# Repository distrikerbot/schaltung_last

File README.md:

# schaltung_last
Schaltung_Last_clean:
KiCad Schemantik and Design of the Digital Power Supply

schaltung_last:
Code from CubeIDE

TODO:
rename file names to be clearer

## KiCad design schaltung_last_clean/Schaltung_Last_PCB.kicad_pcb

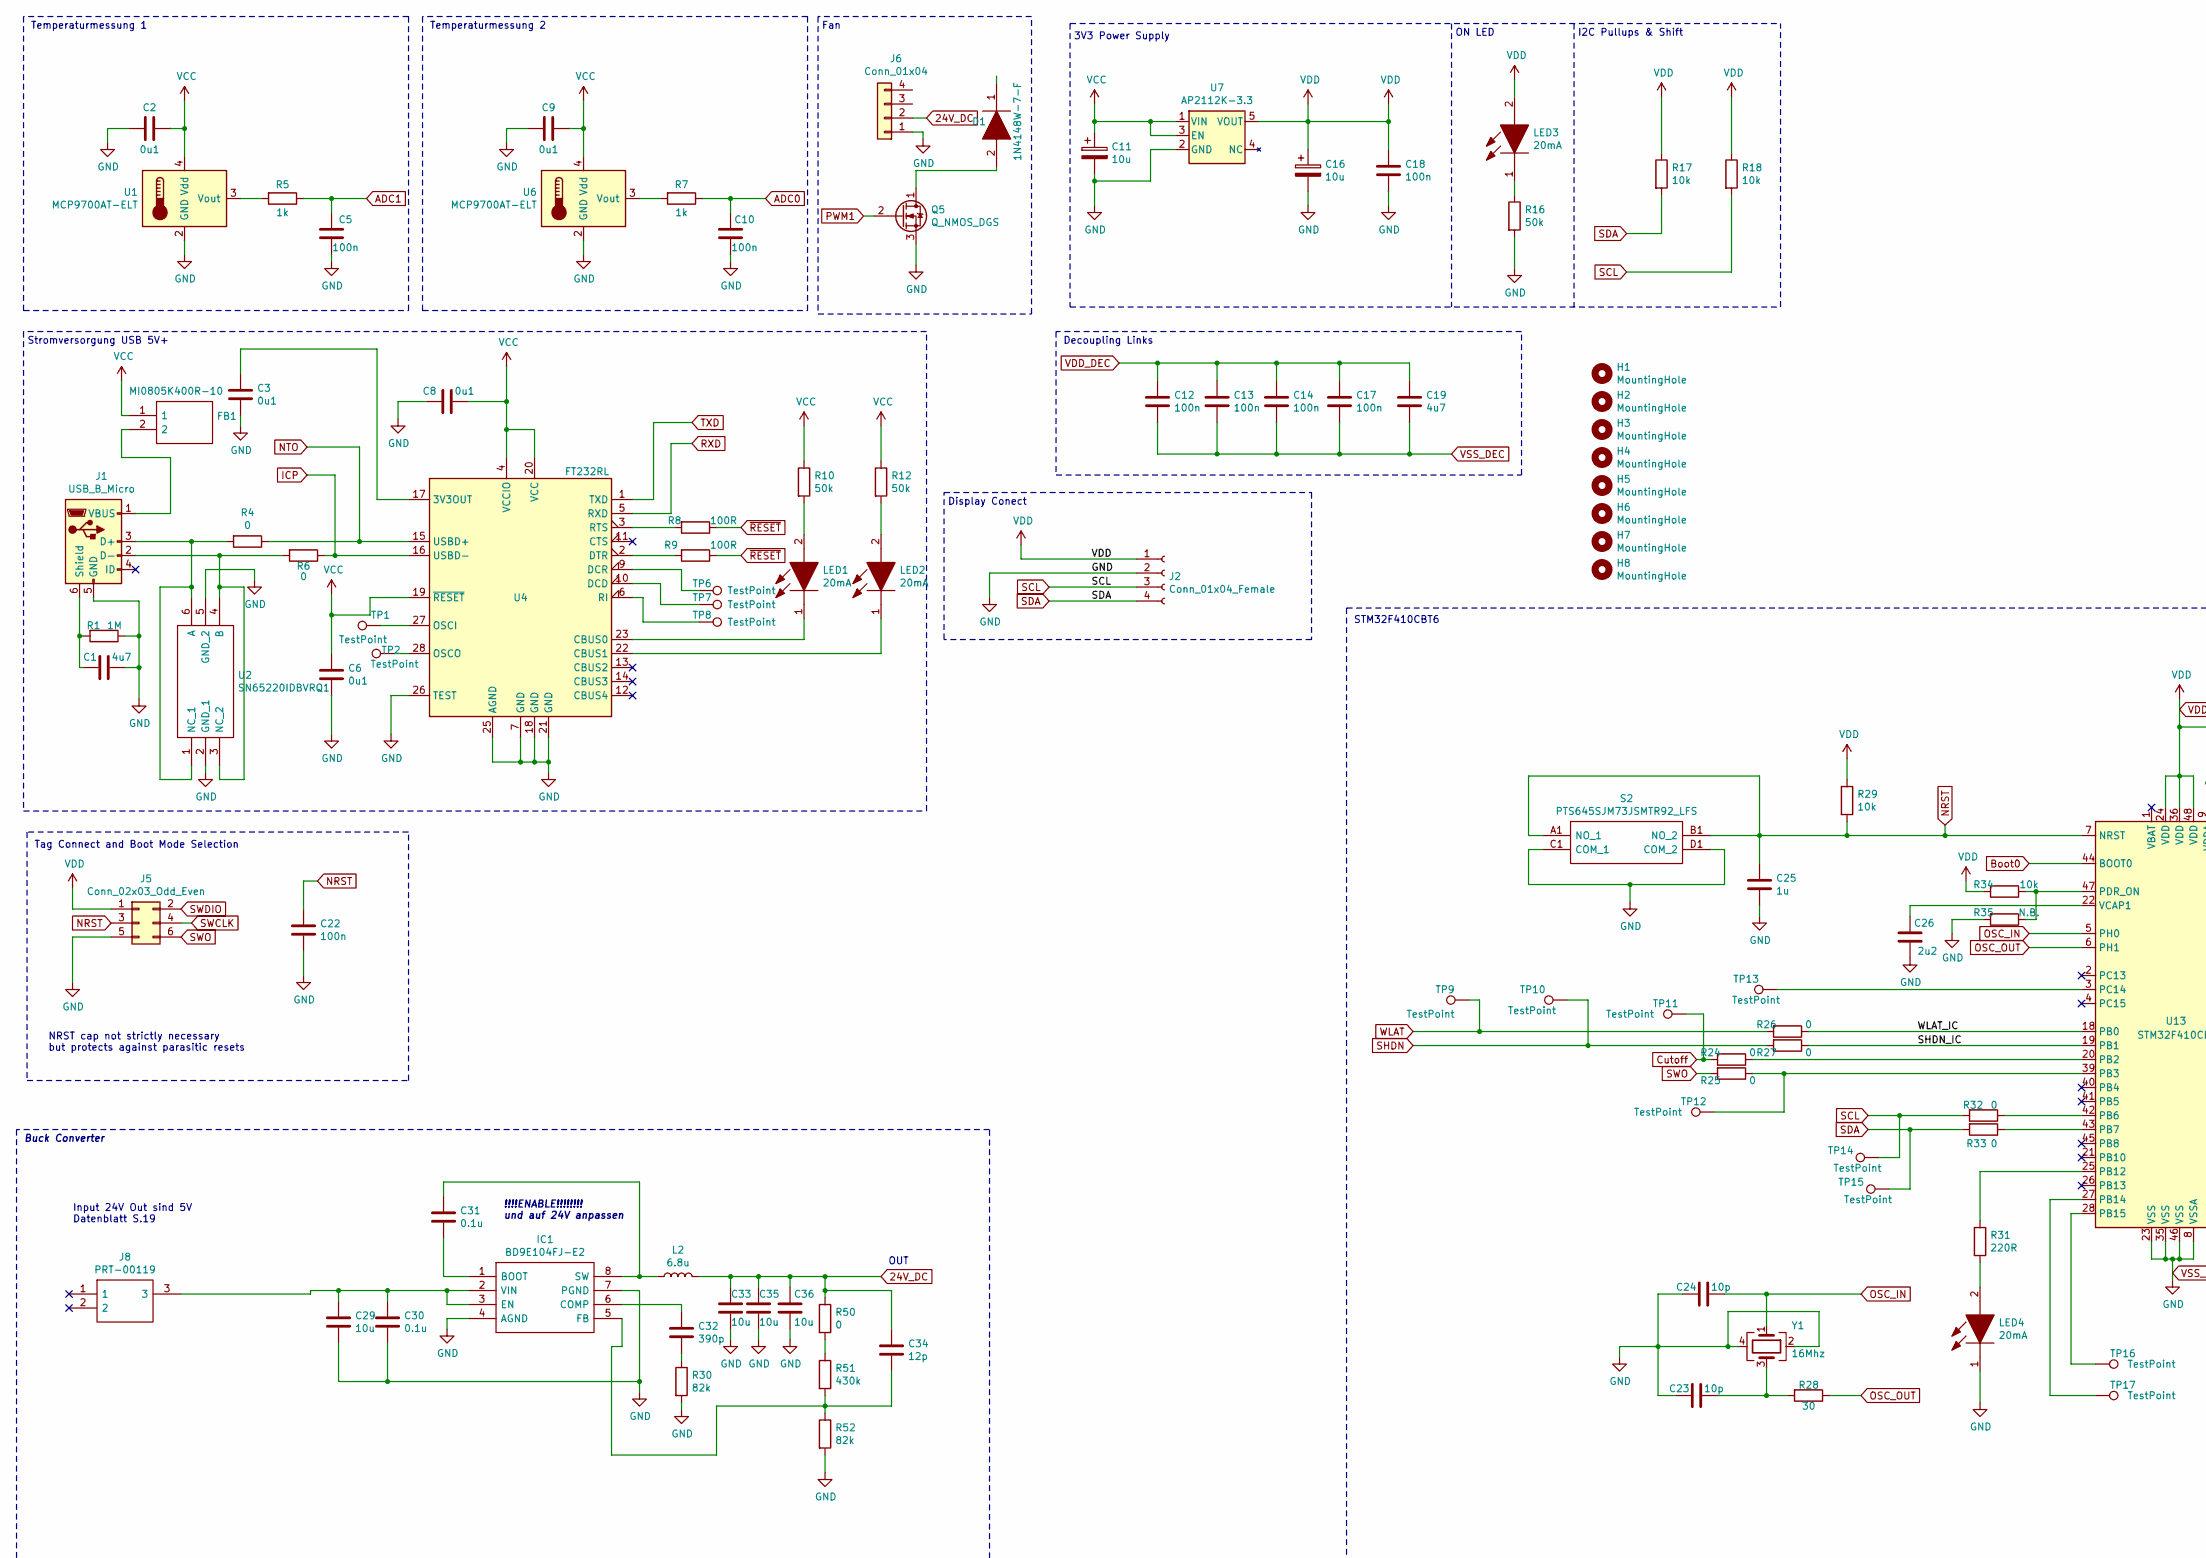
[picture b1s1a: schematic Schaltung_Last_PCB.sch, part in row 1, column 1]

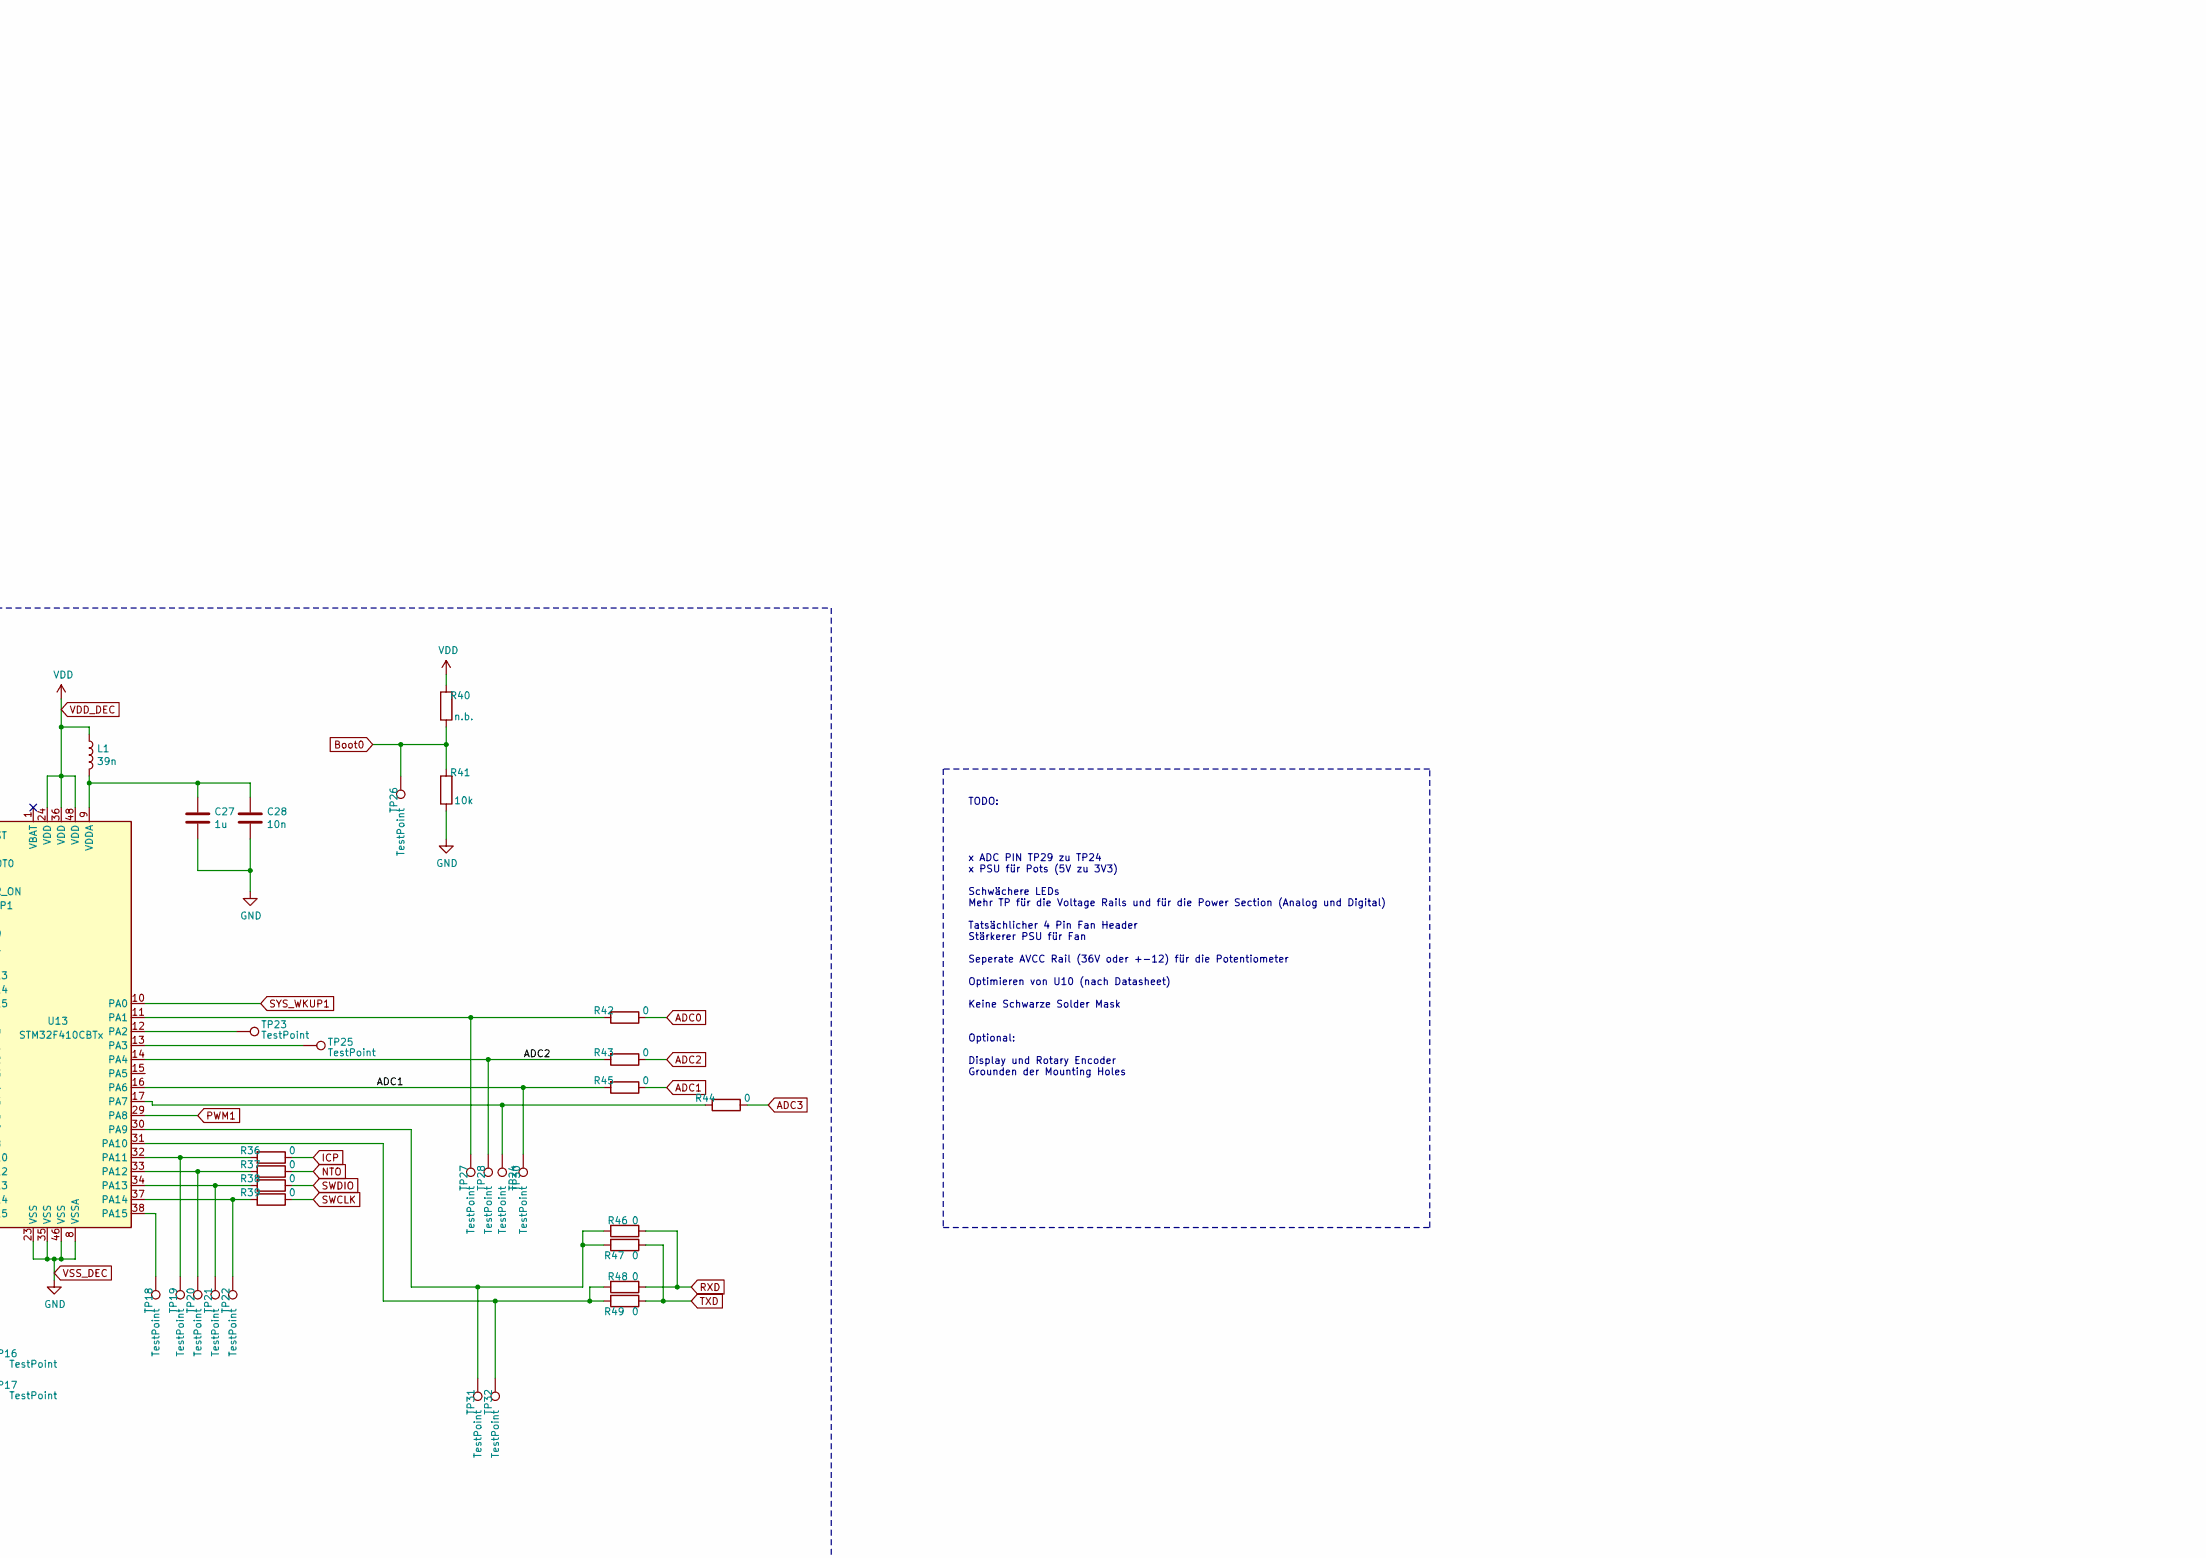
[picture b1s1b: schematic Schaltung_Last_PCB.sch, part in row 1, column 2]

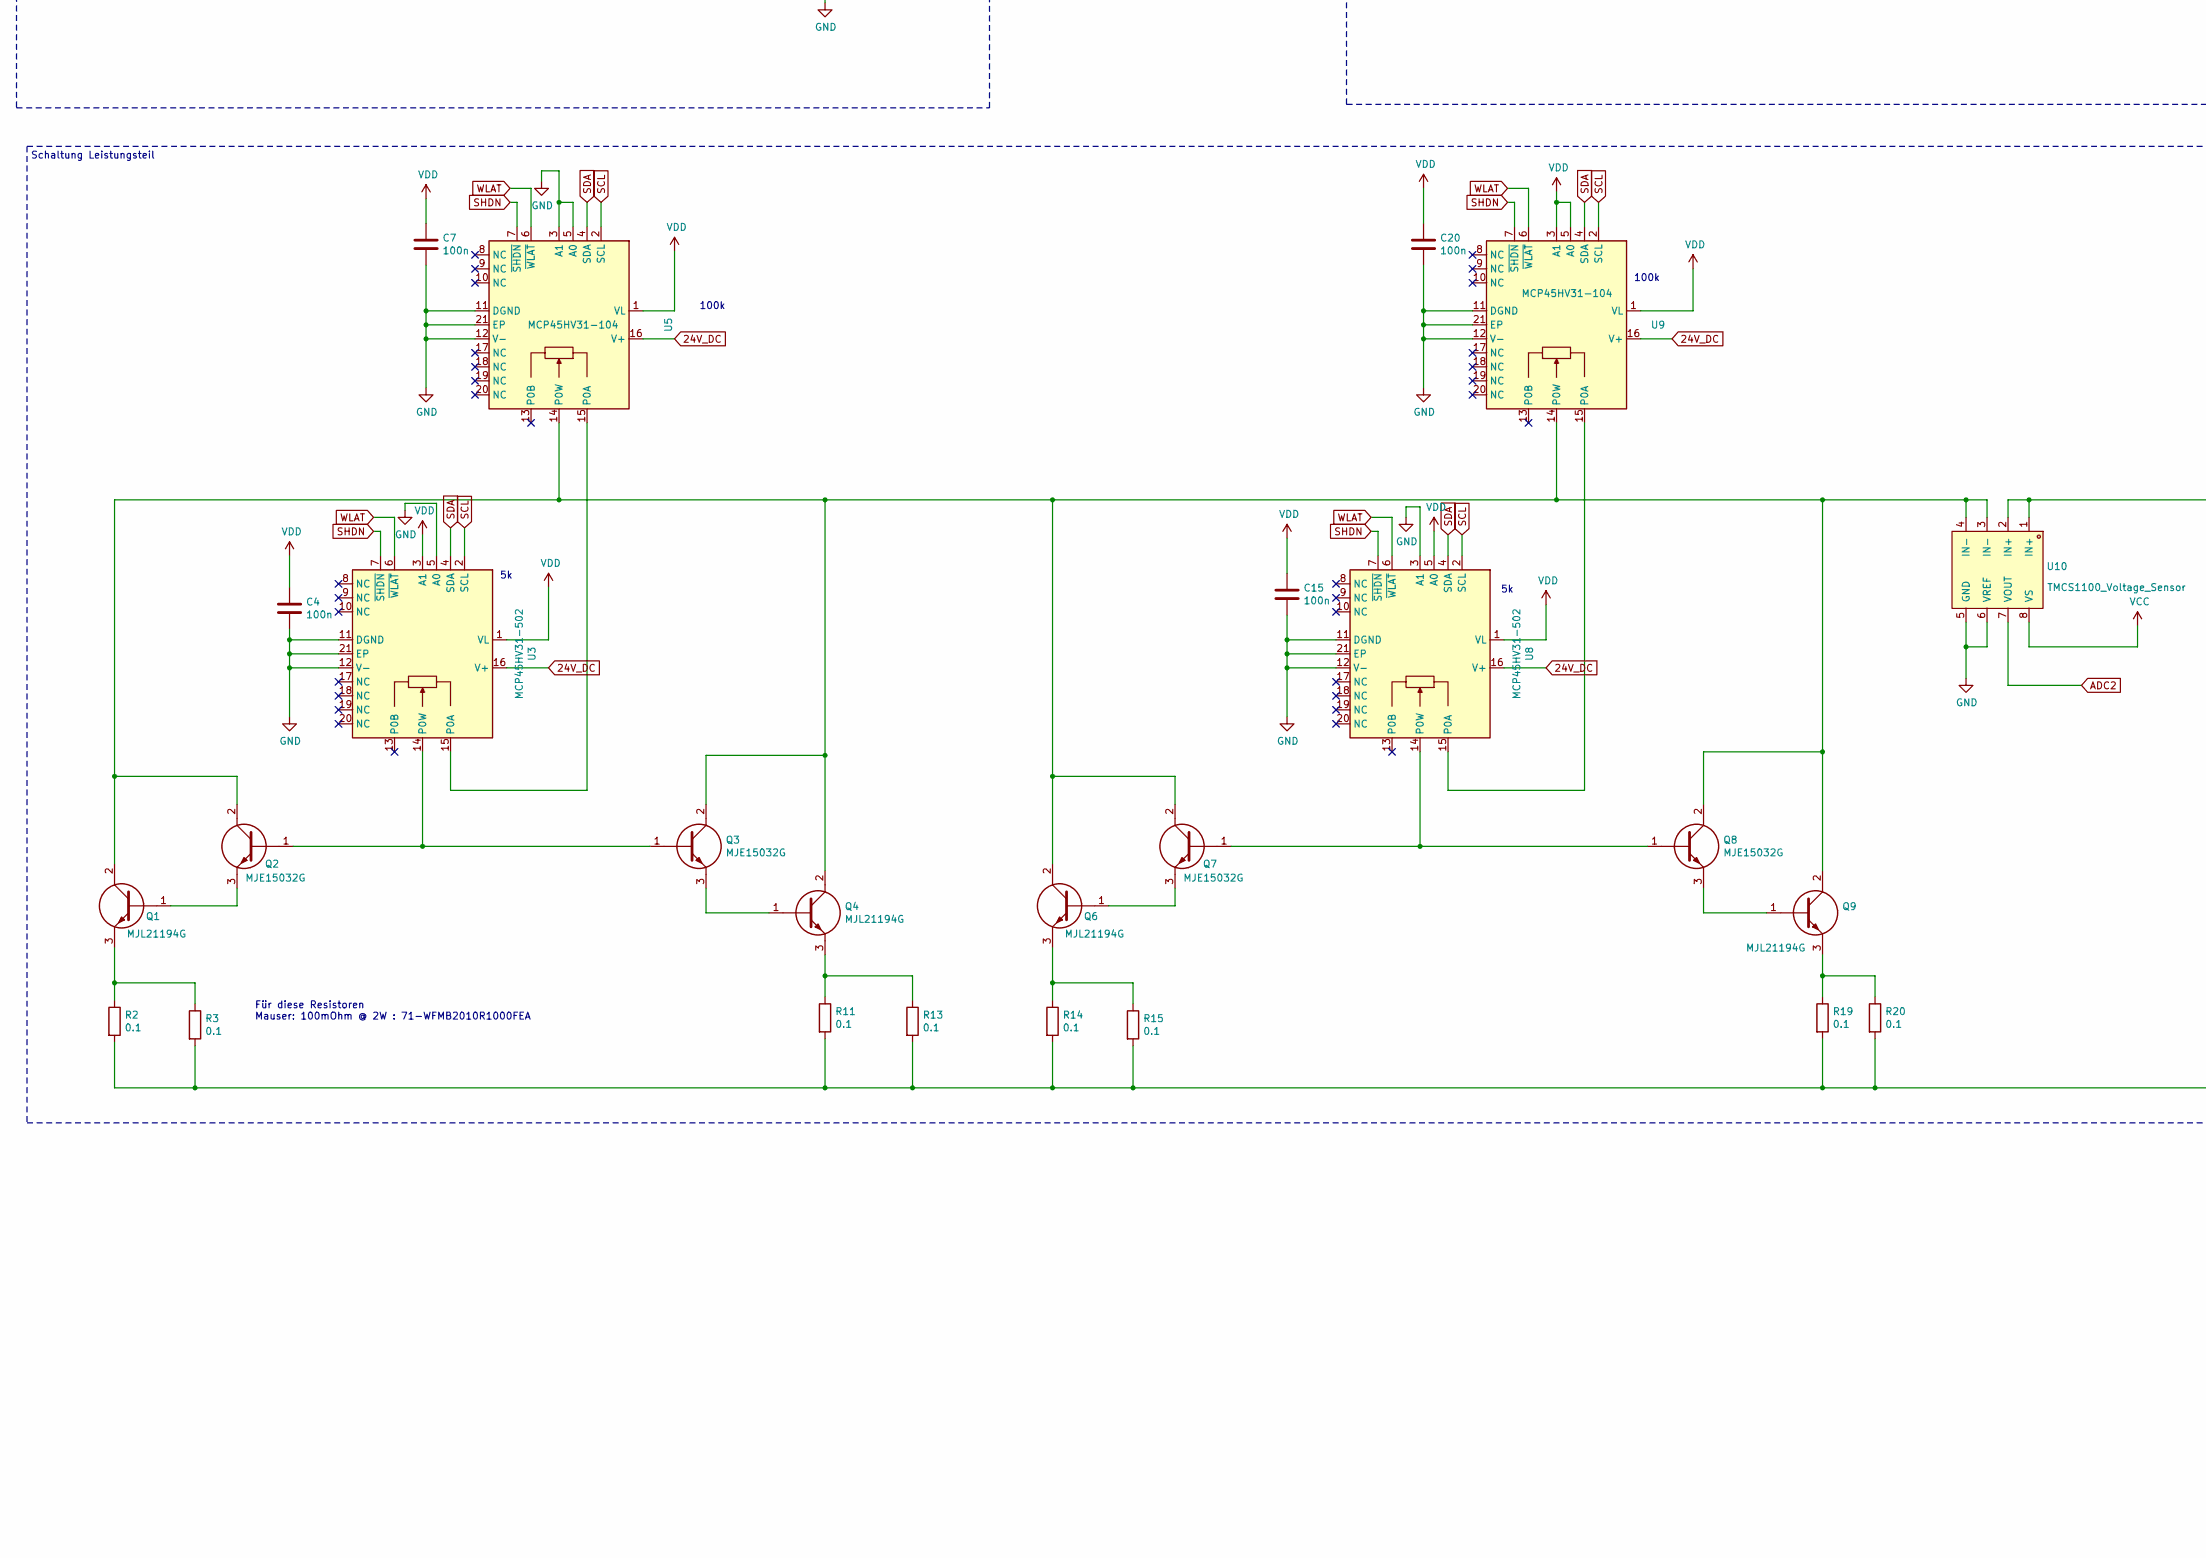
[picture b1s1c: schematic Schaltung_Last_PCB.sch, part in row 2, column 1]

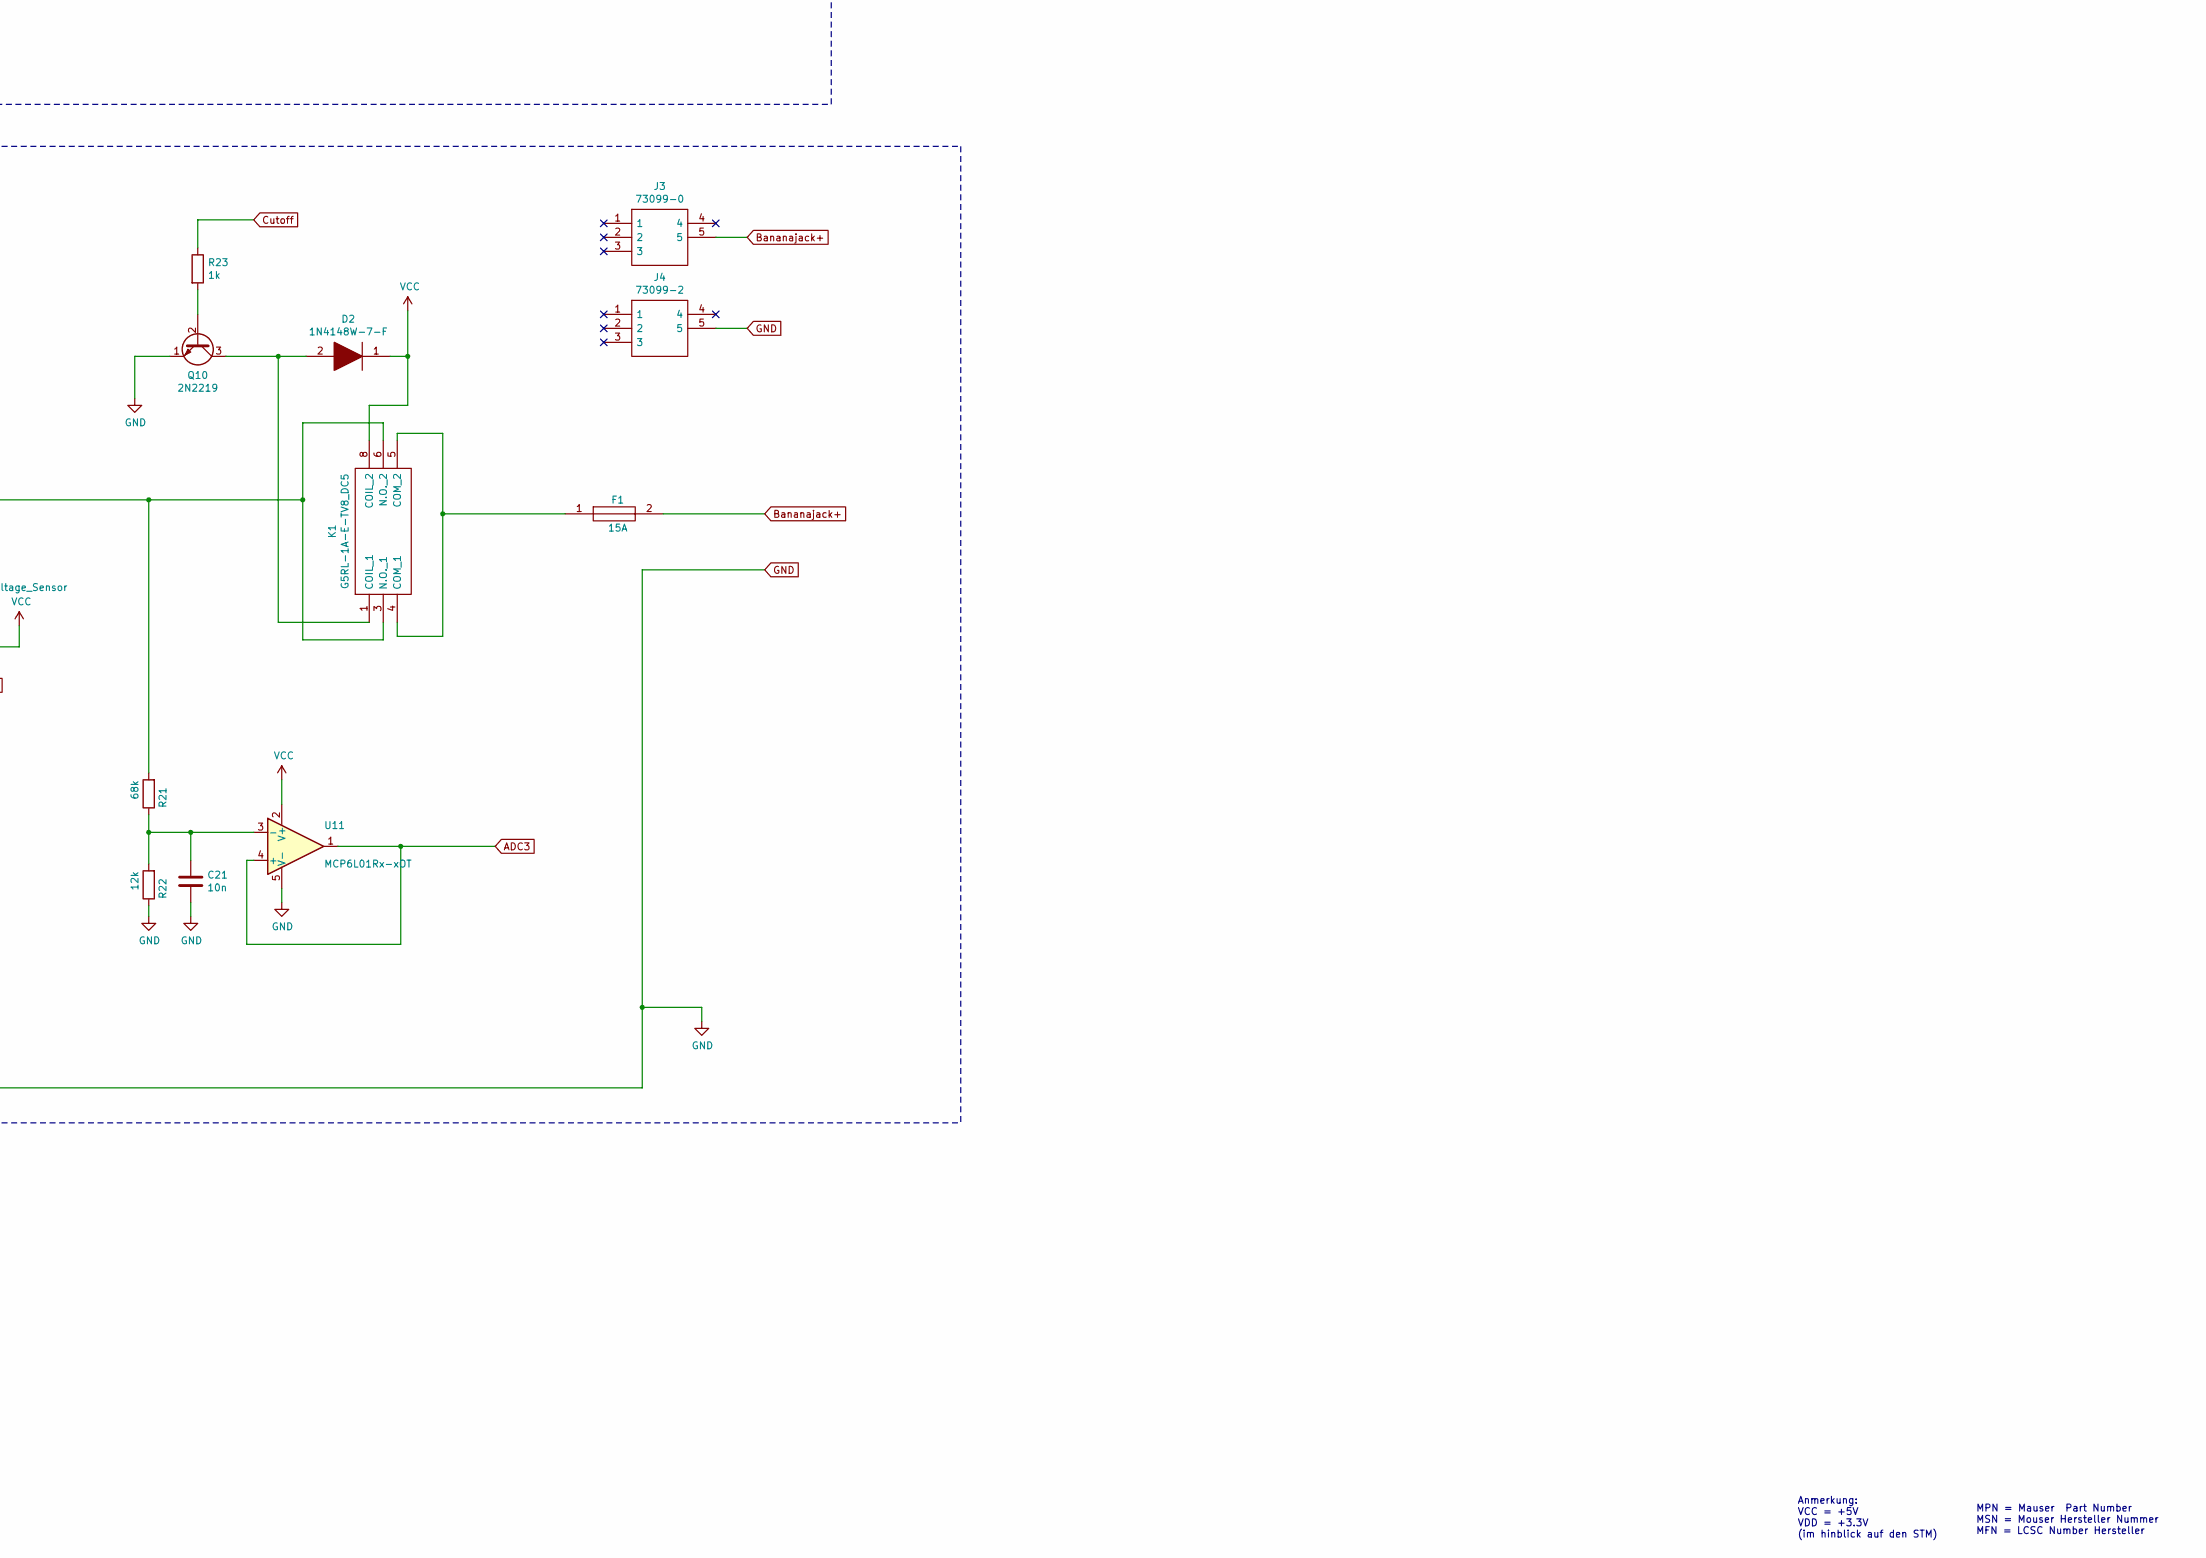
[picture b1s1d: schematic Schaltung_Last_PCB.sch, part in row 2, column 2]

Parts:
C1: 4u7; C_0603_1608Metric; MPN 810-C1608X5R1A475KE
C2, C3, C6, C8, C9: 0u1; C_0603_1608Metric; MPN 581-06035C104JAT4A
C4, C5, C7, C10, C12, C13, C14, C15, C17, C18, C20: 100n; C_0603_1608Metric; MPN 80-C603C104K5RAC3121
C11: 10u; C_Elec_5x5.8; MPN 667-EEE-HB1V100AR
C16: 10u; C_Elec_4x5.8; MPN 667-EEE-FK1E100R
C19: 4u7; C_0805_2012Metric; MPN 963-LMF212B7475KGHT
C21: 10n; C_0805_2012Metric; MPN 603-CC0805KRX77BB103
C22: 100n; C_0805_2012Metric; MPN 581-08055C105K4T4A
C23, C24: 10p; C_0603_1608Metric; MPN 581-06031A8R0CAT2A
C25, C27: 1u; C_0805_2012Metric; MPN 581-08055C105K4T4A
C26: 2u2; C_0603_1608Metric
C28: 10n; C_0603_1608Metric; MPN 81-GCM1887U1H103JA6J
C29, C33, C35, C36: 10u; C_0805_2012Metric
C30, C31: 0.1u; C_0805_2012Metric
C32: 390p; C_0805_2012Metric
C34: 12p; C_0805_2012Metric
D1, D2: 1N4148W-7-F; SOD3716X145N; Mouser Part Number 621-1N4148W-F
F1: 15A; FUSC6127X294N; Mouser Part Number 576-0451015.MRL
FB1: MI0805K400R-10; BEADC2012X110N; Mouser Part Number N/A
H1, H2, H3, H4, H5, H6, H7, H8: MountingHole; MountingHole_3.2mm_M3
IC1: BD9E104FJ-E2; SOIC127P600X165-8N; Mouser Part Number 755-BD9E104FJ-E2
J1: USB_B_Micro; USB_Micro-B_Molex-105017-0001; MPN 538-105017-0001
J2: Conn_01x04_Female; PinSocket_1x04_P2.54mm_Vertical; MPN 855-M20-1060400
J3: 73099-0; 730992; Manufacturer_Part_Number 73099-0; Mouser Part Number 565-73099-0
J4: 73099-2; 730992; Manufacturer_Part_Number 73099-2; Mouser Part Number 565-73099-2
J5: Conn_02x03_Odd_Even; Tag-Connect_TC2030-IDC-NL_2x03_P1.27mm_Vertical
J6: Conn_01x04; PinHeader_1x04_P2.54mm_Vertical
J8: PRT-00119; PRT00119; Mouser Part Number 474-PRT-00119
K1: G5RL-1A-E-TV8_DC5; G5RL1AETV8DC5; Mouser Part Number 653-G5RL1AETV8DC5
L1: 39n; L_0603_1608Metric; MPN 81-LQW18AN39NG00D
L2: 6.8u; L_0603_1608Metric
LED1, LED2, LED3, LED4: 20mA; 155060GS75300; Mouser Part Number 710-155060GS75300
Q1, Q4, Q6, Q9: MJL21194G; TO545P530X1980X2940-3P; Mouser Part Number 863-MJL21194G
Q2, Q3, Q7, Q8: MJE15032G; TO254P483X1010X2035-3P; Mouser Part Number 863-MJE15032G
Q5: Q_NMOS_DGS; TO-92L_Inline; MPN 512-BS170
Q10: 2N2219; TO-220-3_Vertical
R1: 1M; R_1206_3216Metric; MPN 71-CRCW1206-1.0M-E3
R2, R3, R11, R13, R14, R15, R19, R20: 0.1; R_2010_5025Metric; MPN 667-ERJ-L1DKF10CU
R4: 0; R_0603_1608Metric; MPN 71-CRCW06030000Z0EAC
R5, R7, R23: 1k; R_0603_1608Metric; MPN 667-ERJ-UP3D1001V
R6, R24, R25, R26, R27, R32, R33, R36, R37, R38, R39, R42, R43, R44, R45, R46, R47, R48, R49: 0; R_0805_2012Metric; MPN 71-CRCW06030000Z0EAC
R8, R9: 100R; R_0603_1608Metric; MPN 71-CRCW0603100RFKEAC
R10, R12, R16: 50k; R_0603_1608Metric; MPN 71-CRCW0402-50K-E3
R17, R18, R29, R41: 10k; R_0603_1608Metric; MPN 667-ERJ-UP3F1002V
R21: 68k; R_0805_2012Metric; MPN 667-ERJ-6RBD6802V
R22: 12k; R_0805_2012Metric; MPN 667-ERJ-6RBD1202V
R28: 30; R_0603_1608Metric; MPN 667-ERJ-UP3J470V
R30, R52: 82k; R_0805_2012Metric
R31: 220R; R_0603_1608Metric; MPN 667-ERJ-UP3F2200V
R34: 10k; R_0603_1608Metric
R35: N.B.; R_0603_1608Metric
R40: n.b.; R_0603_1608Metric; MPN 667-ERJ-UP3F1002V
R50: 0; R_0805_2012Metric
R51: 430k; R_0805_2012Metric
S2: PTS645SJM73JSMTR92_LFS; PTS645SJM73JSMTR92LFS; Mouser Part Number 611-SJM73JSMTR92LFS
TP1, TP2, TP6, TP7, TP8, TP9, TP10, TP11, TP12, TP13, TP14, TP15, TP16, TP17, TP18, TP19, TP20, TP21, TP22, TP23, TP24, TP25, TP26, TP27, TP28, TP30, TP31, TP32: TestPoint; TestPoint_THTPad_2.5x2.5mm_Drill1.2mm
U1, U6: MCP9700AT-ELT; SOT-353_SC-70-5; MPN 579-MCP9700AT-E/LT
U2: SN65220IDBVRQ1; SOT95P280X145-6N; Mouser Part Number 595-SN65220IDBVRQ1
U3, U8: MCP45HV31-502; QFN-20-1EP_5x5mm_P0.65mm_EP3.35x3.35mm; MPN 579-MCP45HV31-502EMQ
U4: FT232RL; SSOP-28_5.3x10.2mm_P0.65mm; MPN 895-FT232RL
U5, U9: MCP45HV31-104; QFN-20-1EP_5x5mm_P0.65mm_EP3.35x3.35mm; MPN 579-MCP45HV31-104EMQ
U7: AP2112K-3.3; SOT-23-5; MPN 621-AP2112K-3.3TRG1
U10: TMCS1100_Voltage_Sensor; SOIC127P600X175-8N; MPN 595-TMCS1100A3QDR
U11: MCP6L01Rx-xOT; SOT-23-5; MPN 579-MCP6L01RT-E/OT
U13: STM32F410CBTx; LQFP-48_7x7mm_P0.5mm
Y1: 16Mhz; Crystal_SMD_0603-4Pin_6.0x3.5mm; MPN 774-406C35B16M00000

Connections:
24V_DC: C33.1, C34.1, C35.1, C36.1, J6.2, L2.2, R50.1, U3.16 (V+), U5.16 (V+), U8.16 (V+), U9.16 (V+)
/SHDN_IC: R27.1, U13.19 (PB1)
/WLAT_IC: R26.1, U13.18 (PB0)
ADC0: C10.2, R7.1, R42.1
ADC1: C5.2, R5.1, R45.1, R45.2, TP30.1, U13.16 (PA6)
ADC2: R43.1, R43.2, TP28.1, U10.7 (VOUT), U13.14 (PA4)
ADC3: R44.1, U11.1, U11.4 (+)
Bananajack+: F1.2, J3.5
Boot0: R40.1, R41.2, TP26.1, U13.44 (BOOT0)
Cutoff: R23.1, R24.2, TP11.1
GND: C1.1, C2.2, C3.2, C4.1, C5.1, C6.2, C7.1, C8.2, C9.2, C10.1, C11.2, C12.2, C13.2, C14.2, C15.1, C16.2, C17.2, C18.2, C19.2, C20.1, C21.2, C22.2, C23.2, C24.2, C25.2, C26.2, C27.2, C28.2, C29.2, C30.2, C33.2, C35.2, C36.2, IC1.4 (AGND), IC1.7 (PGND), J1.5 (GND), J2.2, J4.5, J5.5, J6.1, LED4.1, Q5.3 (S), Q10.1 (E), R1.1, R2.2, R3.2, R11.2, R13.2, R14.2, R15.2, R16.2, R19.2, R20.2, R22.1, R30.2, R35.2, R41.1, R52.2, S2.C1 (COM_1), S2.D1 (COM_2), U1.2 (GND), U2.2 (GND_1), U2.5 (GND_2), U3.5 (A0), U3.11 (DGND), U3.12 (V-), U3.21 (EP), U4.7 (GND), U4.18 (GND), U4.21 (GND), U4.25 (AGND), U4.26 (TEST), U5.3 (A1), U5.5 (A0), U5.11 (DGND), U5.12 (V-), U5.21 (EP), U6.2 (GND), U7.2 (GND), U8.3 (A1), U8.11 (DGND), U8.12 (V-), U8.21 (EP), U9.11 (DGND), U9.12 (V-), U9.21 (EP), U10.5 (GND), U10.6 (VREF), U11.5 (V-), U13.8 (VSSA), U13.23 (VSS), U13.35 (VSS), U13.46 (VSS), Y1.2, Y1.4
ICP: R6.1, R36.1, U4.16 (USBD-)
NRST: C22.1, C25.1, J5.3, R29.2, S2.A1 (NO_1), S2.B1 (NO_2), U13.7 (NRST)
NTO: R4.1, R37.1, U4.15 (USBD+)
unnamed: C1.2, J1.6 (Shield), R1.2
unnamed: C3.1, U4.17 (3V3OUT)
unnamed: C21.1, R21.1, R22.2, U11.3 (-)
unnamed: C23.1, R28.2, Y1.3
unnamed: C26.1, U13.22 (VCAP1)
unnamed: C27.1, C28.1, L1.2, U13.9 (VDDA)
unnamed: C29.1, C30.1, IC1.2 (VIN), IC1.3 (EN), J8.3
unnamed: C31.1, IC1.8 (SW), L2.1
unnamed: C31.2, IC1.1 (BOOT)
unnamed: C32.1, IC1.6 (COMP)
unnamed: C32.2, R30.1
unnamed: C34.2, IC1.5 (FB), R51.2, R52.1
unnamed: D1.2, Q5.1 (D)
unnamed: D2.2, K1.1 (COIL_1), Q10.3 (C)
unnamed: F1.1, K1.4 (COM_1), K1.5 (COM_2)
unnamed: FB1.2, J1.1 (VBUS)
unnamed: J1.2 (D-), R6.2, U2.3 (NC_2), U2.4 (B)
unnamed: J1.3 (D+), R4.2, U2.1 (NC_1), U2.6 (A)
unnamed: K1.3 (N.O._1), K1.6 (N.O._2), R21.2, U10.1 (IN+), U10.2 (IN+)
unnamed: LED1.1, U4.23 (CBUS0)
unnamed: LED1.2, R10.2
unnamed: LED2.1, U4.22 (CBUS1)
unnamed: LED2.2, R12.2
unnamed: LED3.1, R16.1
unnamed: LED4.2, R31.2
unnamed: Q1.1, Q2.3
unnamed: Q1.2, Q2.2, Q3.2, Q4.2, Q6.2, Q7.2, Q8.2, Q9.2, U5.14 (P0W), U9.14 (P0W), U10.3 (IN-), U10.4 (IN-)
unnamed: Q1.3, R2.1, R3.1
unnamed: Q2.1, Q3.1, U3.14 (P0W)
unnamed: Q3.3, Q4.1
unnamed: Q4.3, R11.1, R13.1
unnamed: Q6.1, Q7.3
unnamed: Q6.3, R14.1, R15.1
unnamed: Q7.1, Q8.1, U8.14 (P0W)
unnamed: Q8.3, Q9.1
unnamed: Q9.3, R19.1, R20.1
unnamed: Q10.2 (B), R23.2
unnamed: R5.2, U1.3 (Vout)
unnamed: R7.2, U6.3 (Vout)
unnamed: R8.2, U4.3 (RTS)
unnamed: R9.2, U4.2 (DTR)
unnamed: R24.1, U13.20 (PB2)
unnamed: R25.1, TP12.1, U13.39 (PB3)
unnamed: R31.1, U13.25 (PB12)
unnamed: R32.1, U13.42 (PB6)
unnamed: R33.1, U13.43 (PB7)
unnamed: R34.1, R35.1, U13.47 (PDR_ON)
unnamed: R36.2, TP19.1, U13.32 (PA11)
unnamed: R37.2, TP20.1, U13.33 (PA12)
unnamed: R38.2, TP21.1, U13.34 (PA13)
unnamed: R39.2, TP22.1, U13.37 (PA14)
unnamed: R42.2, TP27.1, U13.11 (PA1)
unnamed: R44.2, TP24.1, U13.17 (PA7)
unnamed: R46.2, R47.2, TP31.1, U13.30 (PA9)
unnamed: R48.2, R49.2, TP32.1, U13.31 (PA10)
unnamed: R50.2, R51.1
unnamed: TP1.1, U4.27 (OSCI)
unnamed: TP2.1, U4.28 (OSCO)
unnamed: TP6.1, U4.9 (DCR)
unnamed: TP7.1, U4.10 (DCD)
unnamed: TP8.1, U4.6 (RI)
unnamed: TP13.1, U13.3 (PC14)
unnamed: TP16.1, U13.28 (PB15)
unnamed: TP17.1, U13.27 (PB14)
unnamed: TP18.1, U13.38 (PA15)
unnamed: TP23.1, U13.12 (PA2)
unnamed: TP25.1, U13.13 (PA3)
unnamed: U3.15 (P0A), U5.15 (P0A)
unnamed: U8.15 (P0A), U9.15 (P0A)
OSC_IN: C24.1, U13.5 (PH0), Y1.1
OSC_OUT: R28.1, U13.6 (PH1)
PWM1: Q5.2 (G), U13.29 (PA8)
RXD: R46.1, R48.1, U4.5 (RXD)
SCL: J2.3, R18.2, R32.2, TP14.1, U3.2 (SCL), U5.2 (SCL), U8.2 (SCL), U9.2 (SCL)
SDA: J2.4, R17.2, R33.2, TP15.1, U3.4 (SDA), U5.4 (SDA), U8.4 (SDA), U9.4 (SDA)
SHDN: R27.2, TP10.1, U3.7 (~SHDN), U5.7 (~SHDN), U8.7 (~SHDN), U9.7 (~SHDN)
SWCLK: J5.4, R39.1
SWDIO: J5.2, R38.1
SWO: J5.6, R25.2
TXD: R47.1, R49.1, U4.1 (TXD)
VCC: C2.1, C6.1, C8.1, C9.1, C11.1, D2.1, FB1.1, K1.8 (COIL_2), R10.1, R12.1, U1.4 (Vdd), U4.4 (VCCIO), U4.19 (~RESET~), U4.20 (VCC), U6.4 (Vdd), U7.1 (VIN), U7.3 (EN), U10.8 (VS), U11.2 (V+)
VDD_DEC: C4.2, C7.2, C12.1, C13.1, C14.1, C15.2, C16.1, C17.1, C18.1, C19.1, C20.2, J2.1, J5.1, L1.1, LED3.2, R17.1, R18.1, R29.1, R34.2, R40.2, U3.1 (VL), U3.3 (A1), U5.1 (VL), U7.5 (VOUT), U8.1 (VL), U8.5 (A0), U9.1 (VL), U9.3 (A1), U9.5 (A0), U13.24 (VDD), U13.36 (VDD), U13.48 (VDD)
WLAT: R26.2, TP9.1, U3.6 (~WLAT), U5.6 (~WLAT), U8.6 (~WLAT), U9.6 (~WLAT)
~RESET: R8.1, R9.1

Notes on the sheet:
Anmerkung: VCC = +5V VDD = +3.3V (im hinblick auf den STM)
Schaltung Leistungsteil
Stromversorgung USB 5V+
Temperaturmessung 1
Temperaturmessung 2
Fan
3V3 Power Supply
ON LED
I2C Pullups & Shift
Decoupling Links
Display Conect
STM32F410CBT6
Für diese Resistoren Mauser: 100mOhm @ 2W : 71-WFMB2010R1000FEA
MPN = Mauser Part Number MSN = Mouser Hersteller Nummer MFN = LCSC Number Hersteller
NRST cap not strictly necessary but protects against parasitic resets
Tag Connect and Boot Mode Selection
100k
TODO: x ADC PIN TP29 zu TP24 x PSU für Pots (5V zu 3V3) Schwächere LEDs Mehr TP für die Voltage Rails und für die Power Section (Analog und Digital) Tatsächlicher 4 Pin Fan Header Stärkerer PSU für Fan Seperate AVCC Rail (36V oder +-12) für die Potentiometer Optimieren von U10 (nach Datasheet) Kein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
Input 24V Out sind 5V Datenblatt S.19
OUT
!!!!ENABLE!!!!!!!! und auf 24V anpassen
Buck Converter

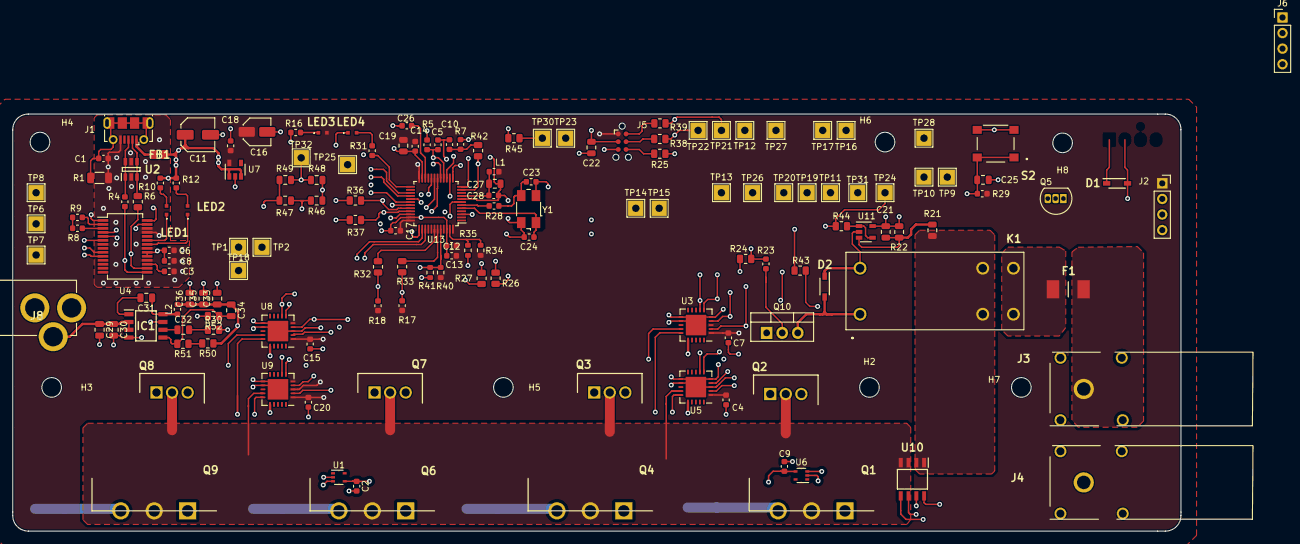
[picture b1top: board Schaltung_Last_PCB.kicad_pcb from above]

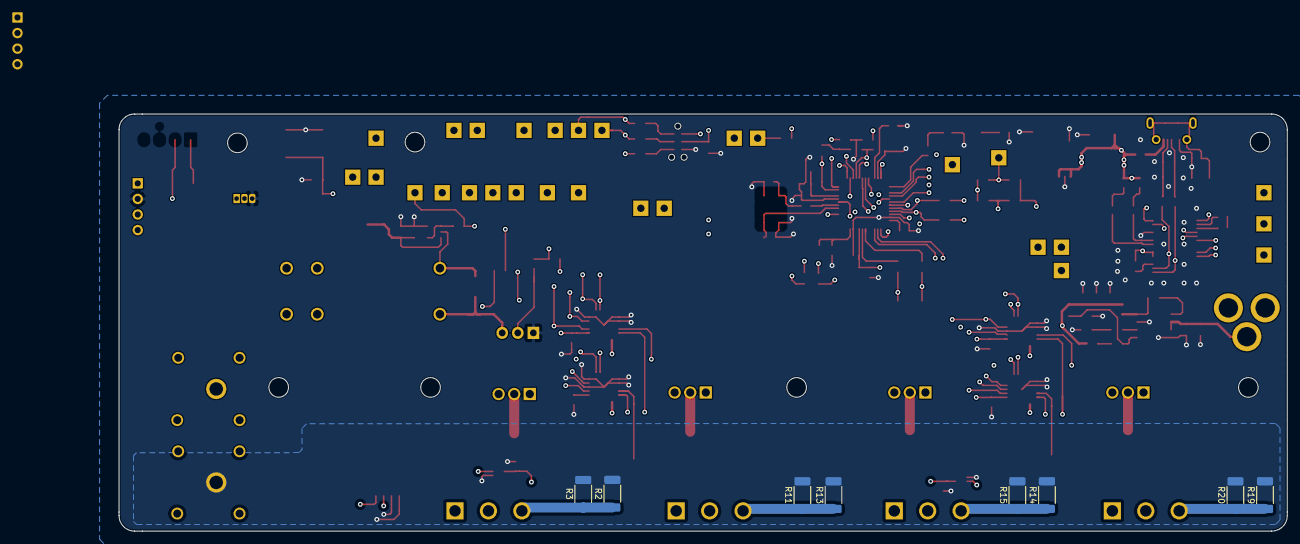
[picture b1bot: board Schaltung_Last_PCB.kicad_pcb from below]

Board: 4 copper layers, 190.5 x 68.0 mm, 166 parts (8 on the bottom side), 98 nets.

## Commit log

2022-01-10 Init
    FIrst init of finished and cleaned project
2022-01-10 Iinit
    Code from Cube IDE innit
